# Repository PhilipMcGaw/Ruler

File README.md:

# Ruler

A KiCad PCB ruler that doubles as a desk reference for SMD footprints, drill sizes, and trace widths—and includes a small ATtiny85 circuit to light five LEDs. Designed by [Philip McGaw](https://philipmcgaw.com).

The board is roughly **100 mm** long and combines measurement scales with populated example parts you can touch, compare, and (optionally) program.

## Features

### Measurement & reference

- **Metric** and **imperial** ruler scales (including 1/8″ and 1/10″ subdivisions)
- **Degree / protractor** scale for rough angle checks
- **Drill hole** reference sizes
- **Trace width** and **font size** guides (mm and mil)
- **SMD resistor** footprints from 0201 through 2512, with separate **hand-solder** and **machine-solder** pad variants
- **SMD LED** examples (0201, 0402, 0603, 0805, 1206)
- **Test points** labelled for common pad/hole diameters (1.0–2.5 mm)

### Electronics

| Item | Details |
|------|---------|
| MCU | ATtiny85V-10SU (SOIJ-8) |
| LEDs | Five, one per common SMD size (red 1206, green 0402, yellow 0603, orange 0805, blue 0201) |
| Power | CR2032 coin cell (Keystone 3002 holder) |
| Programming | 2×3 pin header (`J1`, labelled ICP6) for in-circuit programming |

The populated LEDs are driven by the ATtiny85. **Firmware is not included in this repository**—you will need to write and flash your own sketch (e.g. with [Arduino IDE + ATTinyCore](https://github.com/SpenceKonde/ATTinyCore) or `avrdude` via the ISP header).

> **Note:** This ruler is intended as a **reference and teaching aid**, not a calibrated measuring instrument.

## Repository layout

```
KiCAD/
├── ruler.kicad_pro      # KiCad project
├── ruler.kicad_sch      # Schematic
├── ruler.kicad_pcb      # Board layout
├── Common/              # Project symbols, footprints, design blocks
│   ├── Symbols.kicad_sym
│   ├── Footprints/      # Custom footprints (SquashedFly — https://squashedfly.eu/)
│   └── Design Blocks/
├── Libraries/           # Additional third-party symbol/footprint libraries
├── sym-lib-table
├── fp-lib-table
└── design-block-lib-table
```

Gerber output is configured to write to `KiCAD/Gerber/` when you plot from Pcbnew.

## Requirements

- **[KiCad](https://www.kicad.org/)** 9 or 10 (project files were last saved with KiCad 10)
- **PCBRulers** footprint library — the board uses footprints such as `PCBRulers:Metric_Ruler_96mm`, `PCBRulers:Inch_Ruler_3.5in_10`, `PCBRulers:Drills`, and `PCBRulers:Degree_Scale`. Install the [PCBruler](https://github.com/jbtronics/PCBruler) library (or equivalent) and add it to your KiCad footprint library path if footprints appear missing.
- Standard KiCad libraries for passives, connectors, batteries, and the ATtiny symbol (project rescue lib `ruler-rescue` is embedded in the schematic)

## Opening the project

1. Clone this repository.
2. Open `KiCAD/ruler.kicad_pro` in KiCad.
3. If prompted about missing libraries, confirm that `Common/` paths resolve (they use `${KIPRJMOD}`) and that **PCBRulers** is installed globally or added to `fp-lib-table`.

Project-local tables already point at bundled assets:

- Symbols: `Common/Symbols.kicad_sym`, Partsbox HTTP lib
- Footprints: `Common/Footprints/`

## Building the board

1. Run **Design Rules Check** (DRC) in Pcbnew and resolve any issues for your fab’s capabilities.
2. Generate manufacturing files: **File → Plot** (Gerbers) and **File → Fabrication Outputs → Drill Files**.
3. Order from your preferred PCB fab. For best readability of the silkscreen scales and contact details, **ENIG** finish and a dark soldermask are commonly used on similar rulers.

Populate the optional electronics if you want the LED demo to work; the ruler scales and footprint references are useful even unpopulated.

## Programming the ATtiny85

1. Connect an ISP programmer to `J1` (6-pin, 2.54 mm pitch, 2×3).
2. Power the board from the CR2032 cell or according to your programmer’s requirements.
3. Flash firmware with your toolchain of choice.

Pin mapping and LED connections are defined in `ruler.kicad_sch` / `ruler.kicad_pcb`.

## Credits

- **Design:** Philip McGaw — [philipmcgaw.com](https://philipmcgaw.com) · [GitHub](https://github.com/PhilipMcGaw)
- **[SquashedFly](https://squashedfly.eu/)** — title block worksheet (`KiCAD/Common/Squashed Fly.kicad_wks`) and optional PCB logo footprints (`SquashedFlySilk`, `SquashedFlyCopper`, etc.) in `KiCAD/Common/Footprints/`
- Ruler scale footprints from the **PCBRulers** / [PCBruler](https://github.com/jbtronics/PCBruler) ecosystem

## License

Hardware design files in this repository are licensed under the **[CERN Open Hardware Licence v2 — Strongly Reciprocal (CERN-OHL-S-2.0)](LICENSE)**, an open source hardware license recommended by the [Open Source Hardware Association (OSHWA)](https://oshwa.org/).

- **SPDX identifier:** `CERN-OHL-S-2.0`
- **Copyright:** [Philip McGaw](https://philipmcgaw.com/)
- **Full text:** [LICENSE](LICENSE)

You may use, study, modify, and redistribute the schematic and PCB layout under those terms. **Derivative designs must be released under the same license.** If you share the design or boards built from it, include a copy of the license.

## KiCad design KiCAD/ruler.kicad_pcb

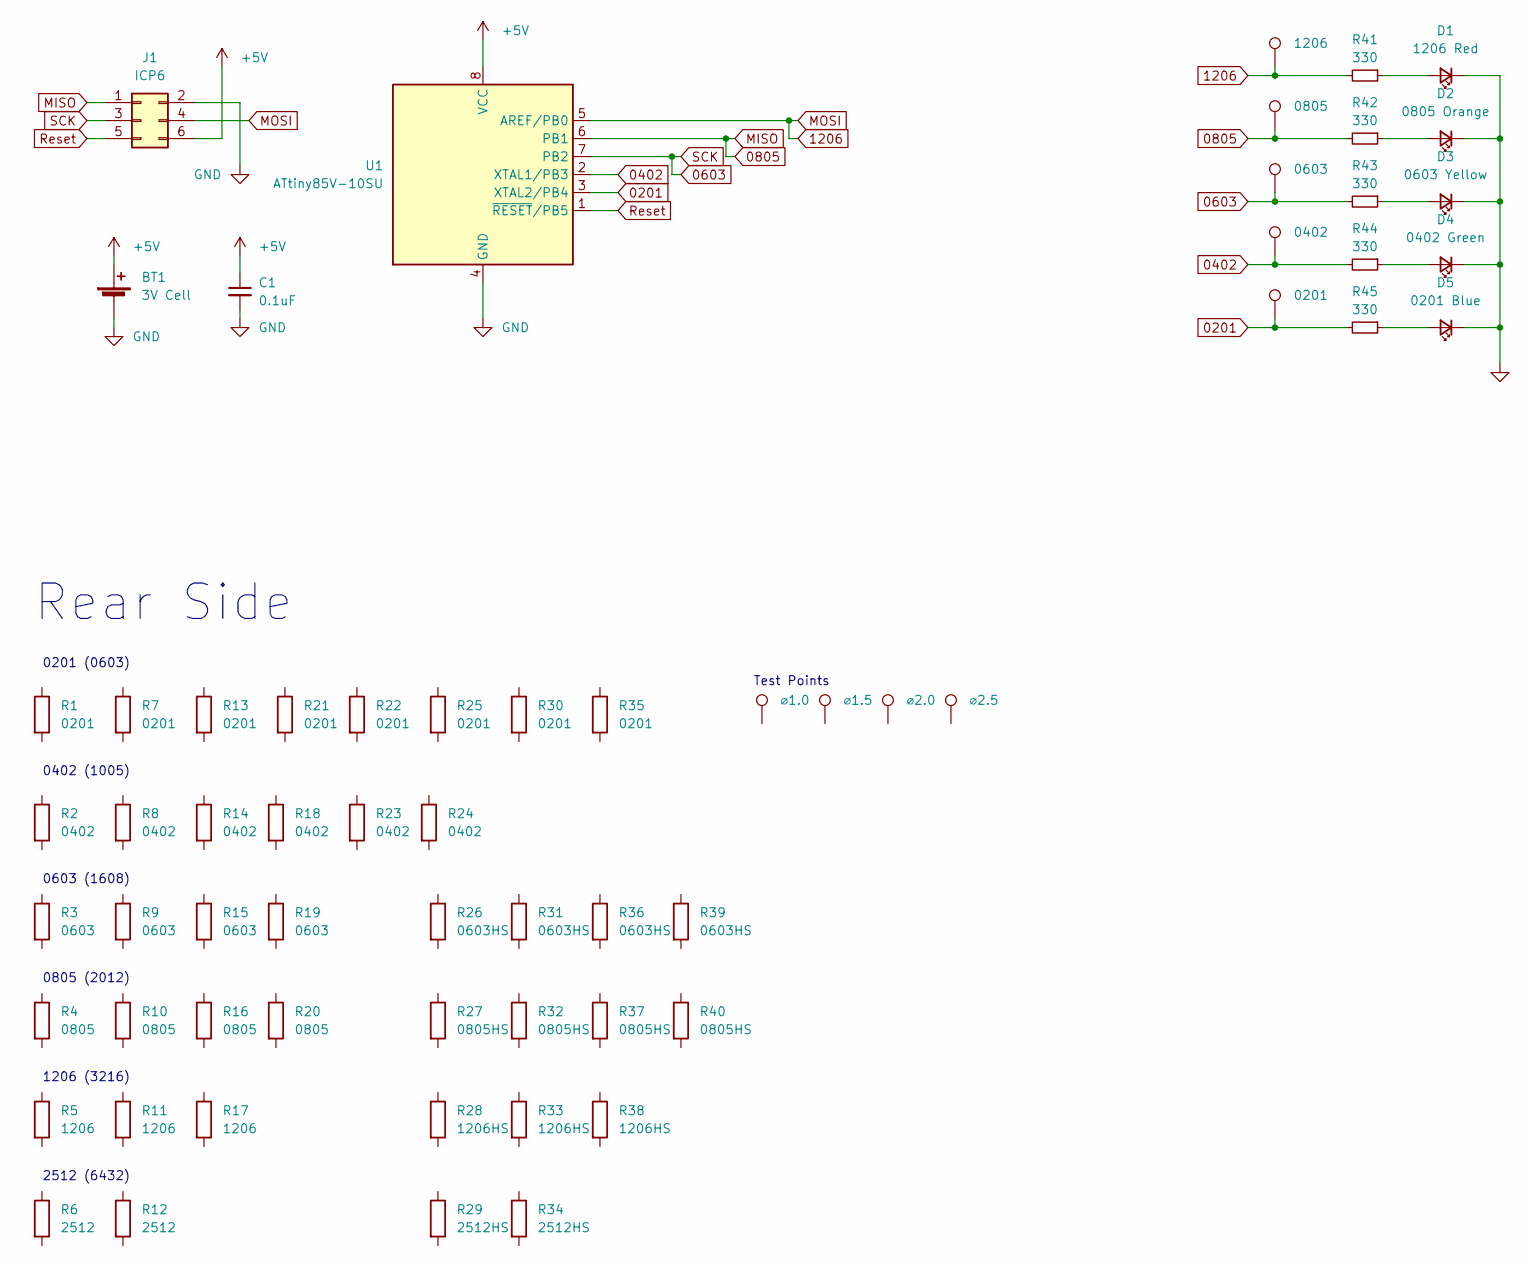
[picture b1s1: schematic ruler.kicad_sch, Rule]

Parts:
BT1: 3V Cell; BatteryHolder_Keystone_3002_1x2032
C1: 0.1uF; C_0805_2012Metric_Pad1.15x1.40mm_HandSolder
D1: 1206 Red; LED_1206_3216Metric_Pad1.42x1.75mm_HandSolder
D2: 0805 Orange; LED_0805_2012Metric_Pad1.15x1.40mm_HandSolder
D3: 0603 Yellow; LED_0603_1608Metric_Pad1.05x0.95mm_HandSolder
D4: 0402 Green; LED_0402_1005Metric
D5: 0201 Blue; LED_0201_0603Metric
J1: ICP6; PinHeader_2x03_P2.54mm_Vertical
R1, R7, R13, R21, R22, R25, R30, R35: 0201; R_0201_0603Metric
R2, R8, R14, R18, R23, R24: 0402; R_0402_1005Metric
R3, R9, R15, R19: 0603; R_0603_1608Metric
R4, R10, R16, R20: 0805; R_0805_2012Metric
R5, R11, R17: 1206; R_1206_3216Metric
R6, R12: 2512; R_2512_6332Metric
R26, R31, R36, R39: 0603HS; R_0603_1608Metric_Pad0.98x0.95mm_HandSolder
R27, R32, R37, R40: 0805HS; R_0805_2012Metric_Pad1.20x1.40mm_HandSolder
R28, R33, R38: 1206HS; R_1206_3216Metric_Pad1.30x1.75mm_HandSolder
R29, R34: 2512HS; R_2512_6332Metric_Pad1.40x3.35mm_HandSolder
R41: 330; R_1206_3216Metric_Pad1.42x1.75mm_HandSolder
R42: 330; R_0805_2012Metric_Pad1.20x1.40mm_HandSolder
R43: 330; R_0603_1608Metric_Pad0.98x0.95mm_HandSolder
R44: 330; R_0402_1005Metric
R45: 330; R_0201_0603Metric
TP1: ⌀1.0; TestPoint_Pad_D1.0mm
TP2: ⌀1.5; TestPoint_Pad_D1.5mm
TP3: ⌀2.0; TestPoint_Pad_D2.0mm
TP4: ⌀2.5; TestPoint_Pad_D2.5mm
TP5: 1206; TestPoint_Pad_D1.0mm
TP6: 0805; TestPoint_Pad_D1.0mm
TP7: 0603; TestPoint_Pad_D1.0mm
TP8: 0402; TestPoint_Pad_D1.0mm
TP9: 0201; TestPoint_Pad_D1.0mm
U1: ATtiny85V-10SU; SOIJ-8_5.3x5.3mm_P1.27mm

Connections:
0201: R45.2, TP9.1 (1_1), U1.3 (XTAL2/PB4)
0402: R44.2, TP8.1 (1_1), U1.2 (XTAL1/PB3)
0603: J1.3, R43.2, TP7.1 (1_1), U1.7 (PB2)
0805: J1.1, R42.2, TP6.1 (1_1), U1.6 (PB1)
1206: J1.4, R41.2, TP5.1 (1_1), U1.5 (AREF/PB0)
+5V: BT1.1 (+), C1.1, J1.6, U1.8 (VCC)
GND: BT1.2 (-), C1.2, D1.1 (K), D2.1 (K), D3.1 (K), D4.1 (K), D5.1 (K), J1.2, U1.4 (GND)
unnamed: D1.2 (A), R41.1
unnamed: D2.2 (A), R42.1
unnamed: D3.2 (A), R43.1
unnamed: D4.2 (A), R44.1
unnamed: D5.2 (A), R45.1
Reset: J1.5, U1.1 (~RESET/PB5)

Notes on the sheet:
0201 (0603)
1206 (3216)
0402 (1005)
Rear Side
Test Points
0805 (2012)
0603 (1608)
2512 (6432)

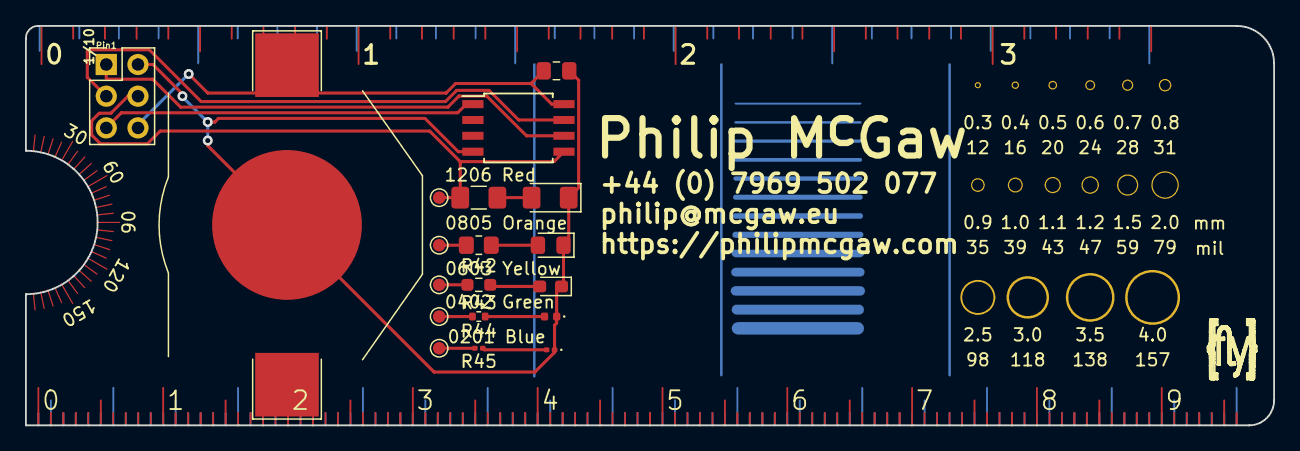
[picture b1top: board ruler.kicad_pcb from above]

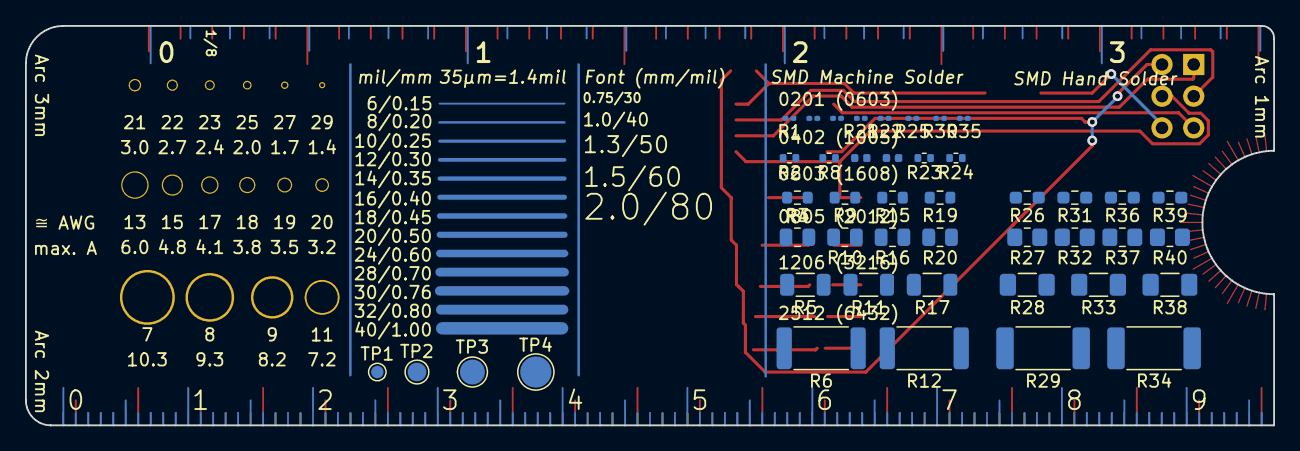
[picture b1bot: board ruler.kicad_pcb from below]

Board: 2 copper layers, 100.0 x 32.0 mm, 63 parts (44 on the bottom side), 13 nets.

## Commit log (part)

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2026-05-28 to fix
2026-05-29 change libs
2026-06-11 edited git ignore and git attributes
